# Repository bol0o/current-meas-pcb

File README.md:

# Current measurement PCB
### AGH Space Systems entry project

*Project was built using KiCad*

This PCB is used to measure current up to 50 amps on high-side (with at least .35mm of solder applied on power traces / **10 amps max without it**).
Voltage should be between 2.7V and 60V.

Analog output of the board is between 0 and 3.25V @ 50amp (with max voltage being clamped to applied VCC).

M2.5 mounting holes are present (36.325mm x 29.500mm center to center)

## Recommended components

| Component nr.   | LCSC part nr. |         Package        |
| --------------- | ------------- | ---------------------- |
| U1              | C44322        | SOT-23-5               |
| R1              | C469426       | 2512                   |
| R2              | C2933305      | 0805                   |
| R3              | C17414        | 0805                   |
| C1              | C49678        | 0805                   |
| C2              | C53134        | 0805                   |
| J1              | C475108       | Through Hole,P=10.16mm |
| J2              | C2937625      | Through Hole,P=2.54mm  |
| D1              | C42445803     | SOD-123                |

## Images

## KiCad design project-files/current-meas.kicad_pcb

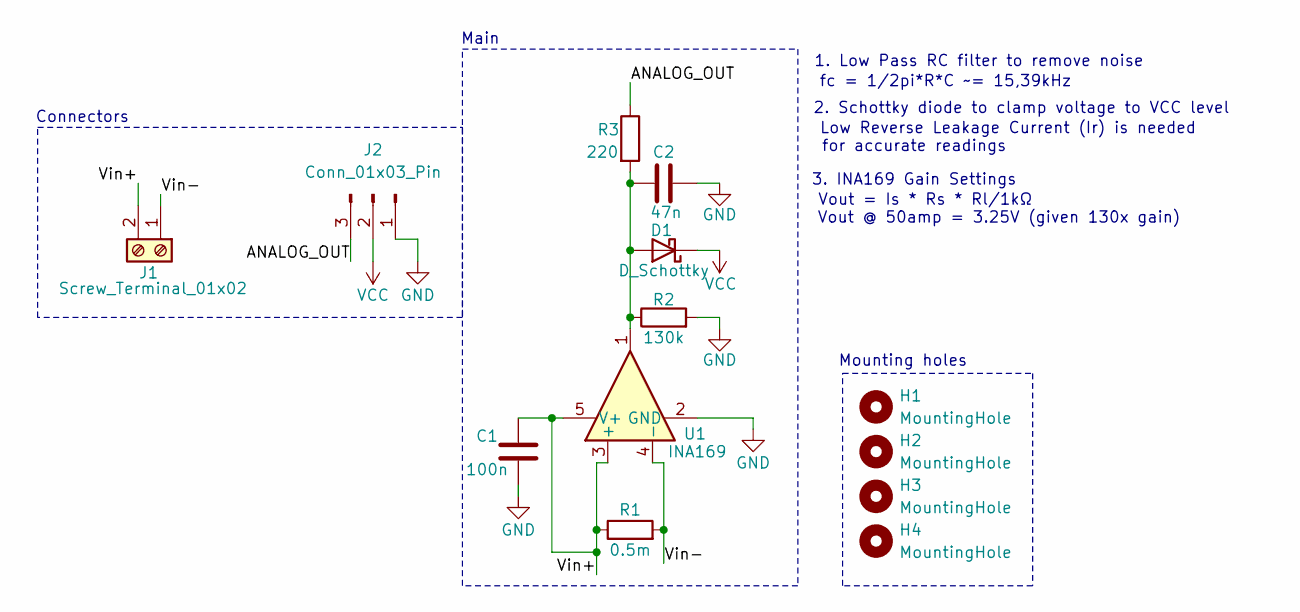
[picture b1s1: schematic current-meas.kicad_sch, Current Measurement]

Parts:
C1: 100n; C_0805_2012Metric
C2: 47n; C_0805_2012Metric
D1: D_Schottky; D_SOD-123
H1, H2, H3, H4: MountingHole; MountingHole_2.7mm_M2.5
J1: Screw_Terminal_01x02; CONN-TH_P10.16_KF135T-10.16-2P
J2: Conn_01x03_Pin; PinHeader_1x03_P2.54mm_Vertical
R1: 0.5m; R_2512_6332Metric
R2: 130k; R_0805_2012Metric
R3: 220; R_0805_2012Metric
U1: INA169; SOT-23-5

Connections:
/ANALOG_OUT: J2.3, R3.1
/Vin+: C1.1, J1.2, R1.1, U1.3 (+), U1.5 (V+)
/Vin-: J1.1, R1.2, U1.4 (-)
GND: C1.2, C2.2, J2.1, R2.2, U1.2 (GND)
unnamed: C2.1, D1.2 (A), R2.1, R3.2, U1.1
VCC: D1.1 (K), J2.2

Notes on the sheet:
Vout @ 50amp = 3.25V (given 130x gain)
Connectors
2. Schottky diode to clamp voltage to VCC level
Vout = Is * Rs * Rl/1kΩ
Main
for accurate readings
1. Low Pass RC filter to remove noise
3. INA169 Gain Settings
fc = 1/2pi*R*C ~= 15,39kHz
Mounting holes
Low Reverse Leakage Current (Ir) is needed

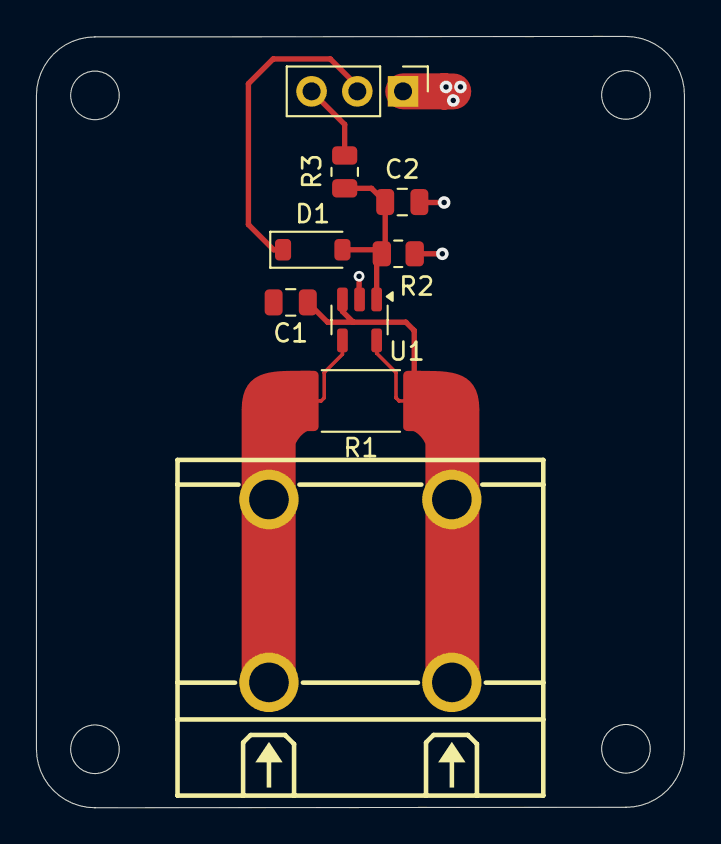
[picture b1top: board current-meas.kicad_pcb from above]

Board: 2 copper layers, 36.0 x 42.8 mm, 13 parts (0 on the bottom side), 6 nets.

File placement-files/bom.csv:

"Reference","Qty","Value","DNP","Exclude from BOM","Exclude from Board","Footprint","Datasheet"
"C1","1","100n","","","","Capacitor_SMD:C_0805_2012Metric","~"
"C2","1","47n","","","","Capacitor_SMD:C_0805_2012Metric","~"
"D1","1","D_Schottky","","","","Diode_SMD:D_SOD-123","~"
"H1,H2,H3,H4","4","MountingHole","","Excluded from BOM","","MountingHole:MountingHole_2.7mm_M2.5","~"
"J1","1","Screw_Terminal_01x02","","","","Custom:CONN-TH_P10.16_KF135T-10.16-2P","~"
"J2","1","Conn_01x03_Pin","","","","Connector_PinHeader_2.54mm:PinHeader_1x03_P2.54mm_Vertical","~"
"R1","1","0.5m","","","","Resistor_SMD:R_2512_6332Metric","~"
"R2","1","130k","","","","Resistor_SMD:R_0805_2012Metric","~"
"R3","1","220","","","","Resistor_SMD:R_0805_2012Metric","~"
"U1","1","INA169","","","","Package_TO_SOT_SMD:SOT-23-5","http://www.ti.com/lit/ds/symlink/ina169.pdf"

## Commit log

2025-11-13 Add gitignore
